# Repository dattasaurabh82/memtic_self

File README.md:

# memtic_self

* [PROJECT PAGE](https://www.dattasaurabh.com/mi-e-metic-self)
* [INSTALLATION GUIDE](https://dattabaumstudio.notion.site/Mimetic-self-Installation-and-Maintenance-Guide-89d1f03d15b848089516b9a0ae4b9f4f?pvs=4)

## System Architecture overview:
```mermaid
sequenceDiagram
    autonumber
    participant Processing_GUI
    participant python_AI_API_req_maker
    participant img_data.json
    participant python_gif_req_maker
    participant gif_data.json
    participant PI_python_OMX_player
    participant HW_swiper

    Note over Processing_GUI: mount network loaction of PI
    loop Every few minutes (configurable in app)
        Processing_GUI->>PI_python_OMX_player:  MQTT: stop omx player

        Note over Processing_GUI: capture image
        
        alt got captions and bounding box
            Processing_GUI->>python_AI_API_req_maker: CMD: raw.png + img_data.json

            activate Processing_GUI

            python_AI_API_req_maker-->>img_data.json: FILE_IO: formatted json response
            
            img_data.json-->>Processing_GUI: FILE_IO:parse a random caption and bounding boxes
            
            Processing_GUI->>python_gif_req_maker: CMD: caption + gif_data.json

            activate python_gif_req_maker

            python_gif_req_maker-->>gif_data.json: FILE_IO: formatted json response

            gif_data.json-->>Processing_GUI: FILE_IO: parse gif url

            deactivate python_gif_req_maker

            Note over Processing_GUI: download gif in network location

            Processing_GUI->>PI_python_OMX_player: CURL: MQTT: start omx player 

            deactivate Processing_GUI

            Note over PI_python_OMX_player: loop new GIF
        
        else caption req error
            Processing_GUI-xpython_AI_API_req_maker: CMD: raw.png + img_data.json

            activate Processing_GUI
            
            python_AI_API_req_maker-ximg_data.json: FILE_IO: exception for json response
            
            Processing_GUI->>PI_python_OMX_player: CURL: show error gif + MQTT: start omx player 

            deactivate Processing_GUI

            Note over PI_python_OMX_player: loop error fixed GIF
        else gif req error
            Processing_GUI->>python_AI_API_req_maker: CMD: raw.png + img_data.json

            activate Processing_GUI
            
            python_AI_API_req_maker->>img_data.json: FILE_IO: exception for json response

            img_data.json-->>Processing_GUI: FILE_IO:parse a random caption and bounding boxes
            
            Processing_GUI-xpython_gif_req_maker: CMD: caption + gif_data.json

            python_gif_req_maker--xgif_data.json: FILE_IO: exception for json response

            Processing_GUI->>PI_python_OMX_player: CURL: show error gif + MQTT: start omx player 

            deactivate Processing_GUI

            Note over PI_python_OMX_player: loop error fixed GIF
        end

        Note over Processing_GUI,HW_swiper: In any case, it send a swipe signal and awaits for swipe finish

        Processing_GUI->>HW_swiper: SERIAL: scroll tiktok
        activate Processing_GUI
       
        Note over HW_swiper: Swipe
        
        activate HW_swiper
        
        HW_swiper->>Processing_GUI: done swipping
        deactivate HW_swiper
        deactivate Processing_GUI
    end
    
```

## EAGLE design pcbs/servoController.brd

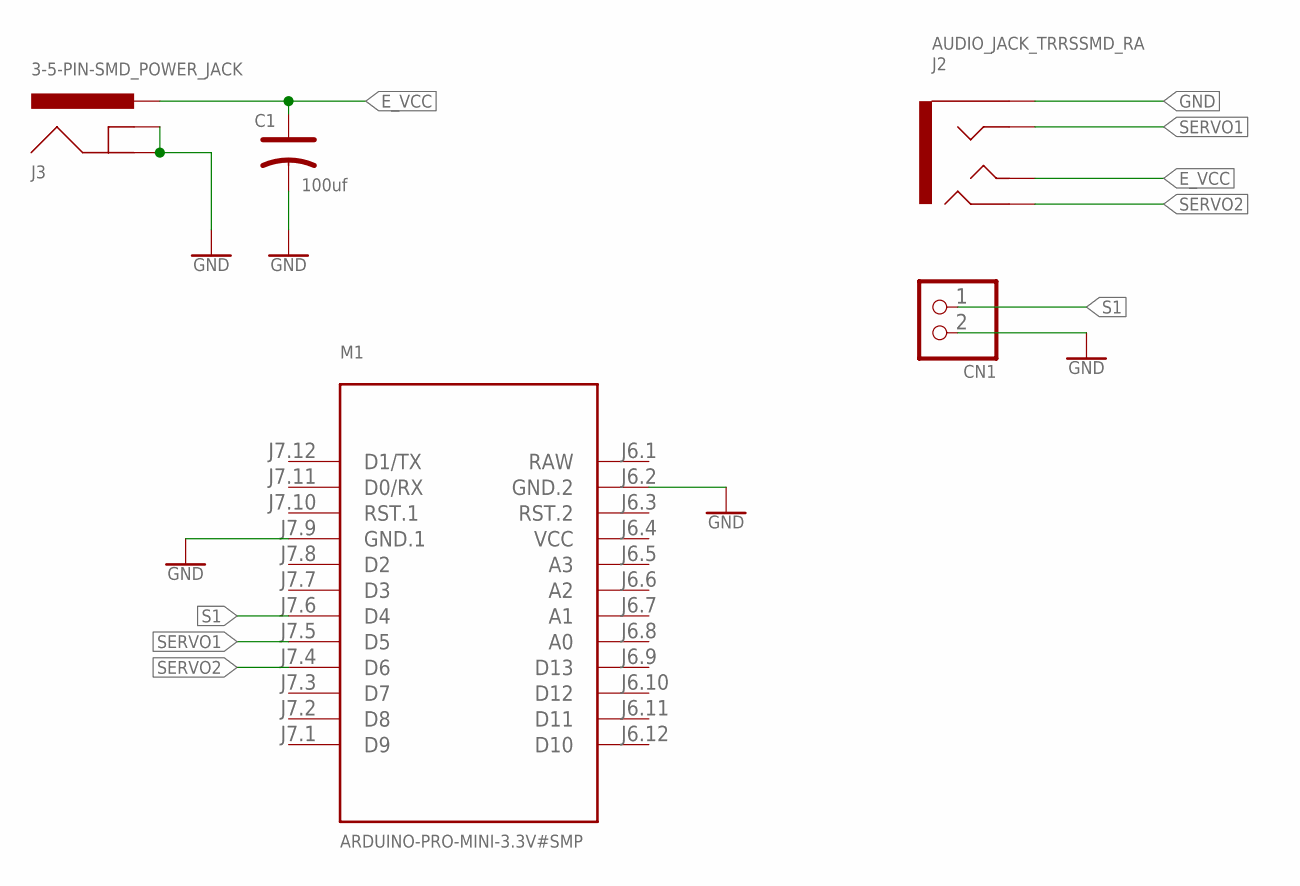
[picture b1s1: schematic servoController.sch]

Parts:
C1: 100uf; PC-D5.3MM
CN1: ARDUINO_3V_TTL_INTERFACE_2_PI_ADAFRUIT_JST_2PIN-S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; ARDUINO_3V_TTL_INTERFACE_2_PI_ADAFRUIT_JST-PH-2-SMT-RA
J2: AUDIO_JACK_TRRSSMD_RA; AUDIO_JACK_3.5MM_TRRS_SMD_RA
J3: 3-5-PIN-SMD_POWER_JACK; 3-5-PIN-SMD_POWER_JACK_PTH
M1: ARDUINO-PRO-MINI-3.3V#SMP; ARDUINO-PRO-MINI#SMP

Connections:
E_VCC: C1.+, J2.TIP, J3.PWR
GND: C1.-, CN1.2 (1), J2.EARTH, J3.GND, J3.GNDBREAK, M1.J6.2 (GND.2), M1.J7.9 (GND.1)
RAW: M1.J6.1 (RAW)
S1: CN1.1 (2), M1.J7.6 (D4)
SERVO1: J2.RING1, M1.J7.5 (D5)
SERVO2: J2.RING2, M1.J7.4 (D6)
VCC: M1.J6.4 (VCC)

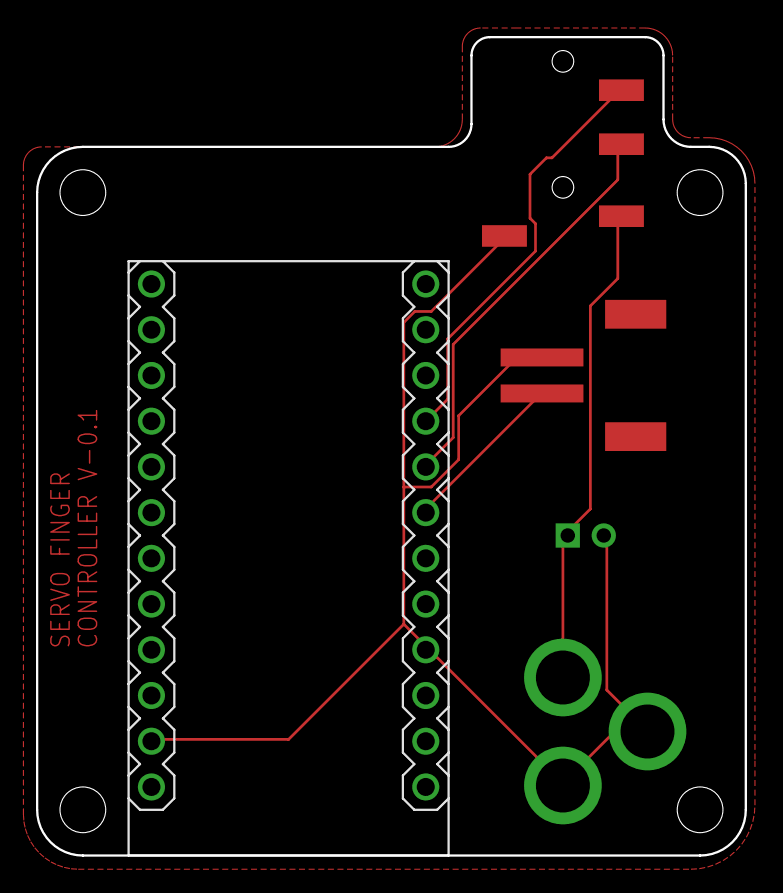
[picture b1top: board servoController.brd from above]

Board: 2 copper layers, 39.4 x 45.5 mm, 5 parts (0 on the bottom side), 5 nets.

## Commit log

2022-05-07 Create LICENSE
2022-05-07 comment
2022-05-07 commented some duplicate stdouts
2022-05-07 delet old json files
2022-05-07 py internal json files path fix
2022-05-09 py modified algo to show more bb
2022-05-09 added logging method
2022-05-09 removed tesrt.py
2022-05-09 system archi verview in readme
2022-05-09 cleanup
